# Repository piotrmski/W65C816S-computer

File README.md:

# W65C816S single-board computer

The following repository documents my novice attempt at designing a microprocessor single-board computer. I had fun putting this design together, however without any prior experience it's left with many flaws which should be addressed if anyone would want to implement it again.

It's a KiCad project, however a single-page PDF of the schematic and gerber files are included, so KiCad is not required to preview it.

### Specs

- W65C816S processor clocked at 10 MHz
- 504 KiB RAM
- 7.75 KiB ROM at half clock speed
- W65C22S peripheral device controller (VIA)
- Dual PS/2 input
- MicroSD input via SPI
- W65C22S's PA6, PA7, PB0-7, CB1, CB2 exposed as general purpose output, intended to drive a character display

### Address space

- 00000-0DFFF - 56 KiB of RAM intended for stack and direct page
- 0E000-0E0FF - I/O (4 least significant bits address VIA, bits 5-7 are unused)
- 0E100-0FFFF - 7.75 KiB of ROM
- 10000-7FFFF - 448 KiB of RAM

### What I think I did right

- It's simple.
- It's compact.
- It's fast.

### Quirks of the design

- In the PCB design many of the components are in DIP packages, my choice of DIP was motivated by the ability to prototype on breadboards.
- In the PCB design capacitors are relatively large to allow hand soldering; resistors are DIP because that's what I had on hand.
- 256 B of ROM (1/32) and 8 KiB of RAM (1/64) are wasted, however I consider it not a big deal.
- Not all SD cards support SPI interface.

### What I did wrong

- The ATF16V8Cs consume unreasonable amounts of energy, glue logic should have been designed with discrete logic gate components.
- Removing and replugging the entire ROM chip to flash it is too fiddly, a programming connector would make programming this device simpler.
- ROM is read only, however it would be simple enough to add a physical switch allowing the processor to write to ROM.

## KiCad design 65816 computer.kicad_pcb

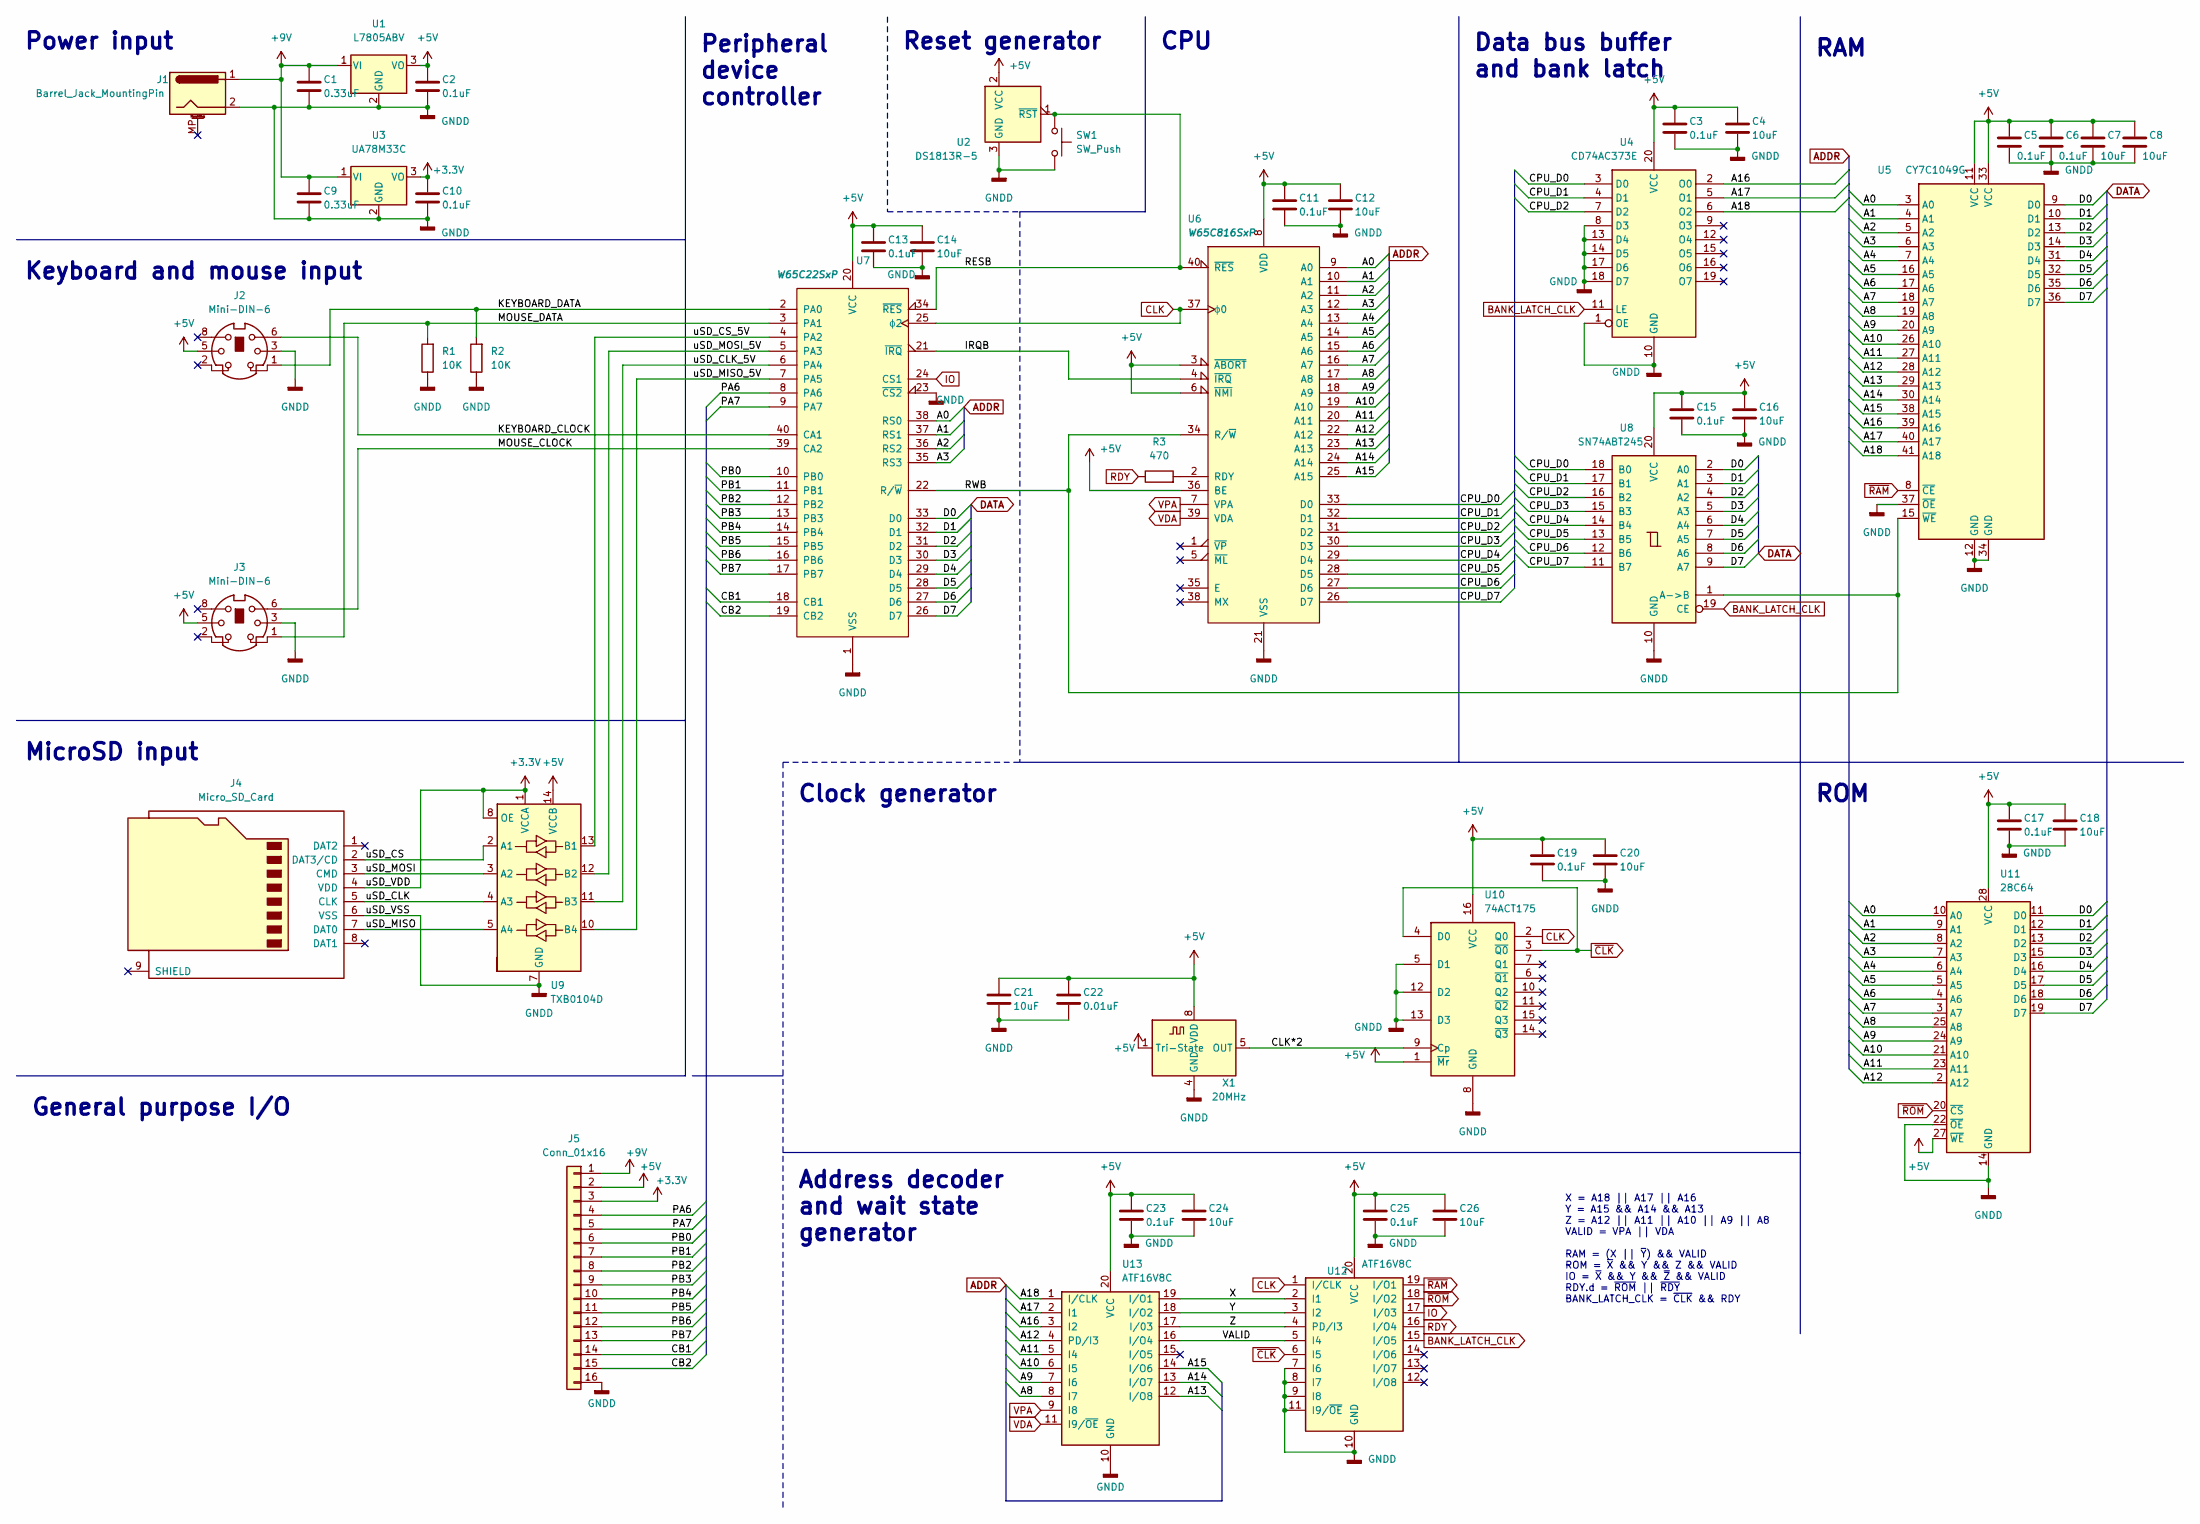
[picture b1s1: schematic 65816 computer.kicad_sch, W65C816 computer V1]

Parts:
C1, C9: 0.33uF; C_1206_3216Metric_Pad1.33x1.80mm_HandSolder
C2, C3, C5, C6, C10, C11, C13, C15, C17, C19, C23, C25: 0.1uF; C_1206_3216Metric_Pad1.33x1.80mm_HandSolder
C4, C7, C8, C12, C14, C16, C18, C20, C21, C24, C26: 10uF; C_1206_3216Metric_Pad1.33x1.80mm_HandSolder
C22: 0.01uF; C_1206_3216Metric_Pad1.33x1.80mm_HandSolder
J1: Barrel_Jack_MountingPin; BarrelJack_GCT_DCJ200-10-A_Horizontal
J2, J3: Mini-DIN-6; KMDGX6SBS
J4: Micro_SD_Card; microSD_HC_Wuerth_693072010801
J5: Conn_01x16; PinHeader_1x16_P2.54mm_Vertical
R1, R2: 10K; R_Axial_DIN0207_L6.3mm_D2.5mm_P7.62mm_Horizontal
R3: 470; R_Axial_DIN0207_L6.3mm_D2.5mm_P7.62mm_Horizontal
SW1: SW_Push; SW_PUSH_6mm
U1: L7805ABV; TO-220-3_Vertical
U2: DS1813R-5; SOT-23
U3: UA78M33C; TO-252-2
U4: CD74AC373E; DIP-20_W7.62mm_Socket_LongPads
U5: CY7C1049G; TSOP-II-44_10.16x18.41mm_P0.8mm
U6: W65C816SxP; DIP-40_W15.24mm_Socket_LongPads
U7: W65C22SxP; DIP-40_W15.24mm_Socket_LongPads
U8: SN74ABT245; DIP-20_W7.62mm_Socket_LongPads
U9: TXB0104D; SOIC-14_3.9x8.7mm_P1.27mm
U10: 74ACT175; DIP-16_W7.62mm_Socket_LongPads
U11: 28C64; DIP-28_W15.24mm_Socket_LongPads
U12, U13: ATF16V8C; DIP-20_W7.62mm_Socket_LongPads
X1: 20MHz; Oscillator_DIP-8

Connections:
+3V3: C10.1, J4.4 (VDD), J5.3, U3.3 (VO), U9.1 (VCCA), U9.8 (OE)
+5V: C2.1, C3.1, C4.1, C5.1, C6.1, C7.1, C8.1, C11.1, C12.1, C13.1, C14.1, C15.1, C16.1, C17.1, C18.1, C19.1, C20.1, C21.1, C22.1, C23.1, C24.1, C25.1, C26.1, J2.5, J3.5, J5.2, U1.3 (VO), U2.2 (VCC), U4.20 (VCC), U5.11 (VCC), U5.33 (VCC), U6.3 (~ABORT), U6.6 (~NMI), U6.8 (VDD), U6.36 (BE), U7.20 (VCC), U8.20 (VCC), U9.14 (VCCB), U10.1 (~Mr), U10.16 (VCC), U11.27 (~WE), U11.28 (VCC), U12.20 (VCC), U13.20 (VCC), X1.1 (Tri-State), X1.8 (VDD)
+9V: C1.1, C9.1, J1.1, J5.1, U1.1 (VI), U3.1 (VI)
/A0: U5.3 (A0), U6.9 (A0), U7.38 (RS0), U11.10 (A0)
/A1: U5.4 (A1), U6.10 (A1), U7.37 (RS1), U11.9 (A1)
/A2: U5.5 (A2), U6.11 (A2), U7.36 (RS2), U11.8 (A2)
/A3: U5.6 (A3), U6.12 (A3), U7.35 (RS3), U11.7 (A3)
/A4: U5.7 (A4), U6.13 (A4), U11.6 (A4)
/A5: U5.16 (A5), U6.14 (A5), U11.5 (A5)
/A6: U5.17 (A6), U6.15 (A6), U11.4 (A6)
/A7: U5.18 (A7), U6.16 (A7), U11.3 (A7)
/A8: U5.19 (A8), U6.17 (A8), U11.25 (A8), U13.8 (I7)
/A9: U5.20 (A9), U6.18 (A9), U11.24 (A9), U13.7 (I6)
/A10: U5.26 (A10), U6.19 (A10), U11.21 (A10), U13.6 (I5)
/A11: U5.27 (A11), U6.20 (A11), U11.23 (A11), U13.5 (I4)
/A12: U5.28 (A12), U6.22 (A12), U11.2 (A12), U13.4 (PD/I3)
/A13: U5.29 (A13), U6.23 (A13), U13.12 (I/O8)
/A14: U5.30 (A14), U6.24 (A14), U13.13 (I/O7)
/A15: U5.38 (A15), U6.25 (A15), U13.14 (I/O6)
/A16: U4.2 (O0), U5.39 (A16), U13.3 (I2)
/A17: U4.5 (O1), U5.40 (A17), U13.2 (I1)
/A18: U4.6 (O2), U5.41 (A18), U13.1 (I/CLK)
/CB1: J5.14, U7.18 (CB1)
/CB2: J5.15, U7.19 (CB2)
/CLK*2: U10.9 (Cp), X1.5 (OUT)
/CPU_D0: U4.3 (D0), U6.33 (D0), U8.18 (B0)
/CPU_D1: U4.4 (D1), U6.32 (D1), U8.17 (B1)
/CPU_D2: U4.7 (D2), U6.31 (D2), U8.16 (B2)
/CPU_D3: U6.30 (D3), U8.15 (B3)
/CPU_D4: U6.29 (D4), U8.14 (B4)
/CPU_D5: U6.28 (D5), U8.13 (B5)
/CPU_D6: U6.27 (D6), U8.12 (B6)
/CPU_D7: U6.26 (D7), U8.11 (B7)
/D0: U5.9 (D0), U7.33 (D0), U8.2 (A0), U11.11 (D0)
/D1: U5.10 (D1), U7.32 (D1), U8.3 (A1), U11.12 (D1)
/D2: U5.13 (D2), U7.31 (D2), U8.4 (A2), U11.13 (D2)
/D3: U5.14 (D3), U7.30 (D3), U8.5 (A3), U11.15 (D3)
/D4: U5.31 (D4), U7.29 (D4), U8.6 (A4), U11.16 (D4)
/D5: U5.32 (D5), U7.28 (D5), U8.7 (A5), U11.17 (D5)
/D6: U5.35 (D6), U7.27 (D6), U8.8 (A6), U11.18 (D6)
/D7: U5.36 (D7), U7.26 (D7), U8.9 (A7), U11.19 (D7)
/IRQB: U6.4 (~IRQ), U7.21 (~IRQ)
/KEYBOARD_CLOCK: J2.6, U7.40 (CA1)
/KEYBOARD_DATA: J2.1, R2.2, U7.2 (PA0)
/MOUSE_CLOCK: J3.6, U7.39 (CA2)
/MOUSE_DATA: J3.1, R1.2, U7.3 (PA1)
/PA6: J5.4, U7.8 (PA6)
/PA7: J5.5, U7.9 (PA7)
/PB0: J5.6, U7.10 (PB0)
/PB1: J5.7, U7.11 (PB1)
/PB2: J5.8, U7.12 (PB2)
/PB3: J5.9, U7.13 (PB3)
/PB4: J5.10, U7.14 (PB4)
/PB5: J5.11, U7.15 (PB5)
/PB6: J5.12, U7.16 (PB6)
/PB7: J5.13, U7.17 (PB7)
/RESB: SW1.1, U2.1 (~RST), U6.40 (~RES), U7.34 (~RES)
/RWB: U5.15 (~WE), U6.34 (R/~W), U7.22 (R/~W), U8.1 (A->B)
/VALID: U12.5 (I4), U13.16 (I/O4)
/X: U12.2 (I1), U13.19 (I/O1)
/Y: U12.3 (I2), U13.18 (I/O2)
/Z: U12.4 (PD/I3), U13.17 (I/03)
/uSD_CLK: J4.5 (CLK), U9.4 (A3)
/uSD_CLK_5V: U7.6 (PA4), U9.11 (B3)
/uSD_CS: J4.2 (DAT3/CD), U9.2 (A1)
/uSD_CS_5V: U7.4 (PA2), U9.13 (B1)
/uSD_MISO: J4.7 (DAT0), U9.5 (A4)
/uSD_MISO_5V: U7.7 (PA5), U9.10 (B4)
/uSD_MOSI: J4.3 (CMD), U9.3 (A2)
/uSD_MOSI_5V: U7.5 (PA3), U9.12 (B2)
BANK_LATCH_CLK: U4.11 (LE), U8.19 (CE), U12.15 (I/O5)
CLK: U6.37 (ϕ0), U7.25 (ϕ2), U10.2 (Q0), U12.1 (I/CLK)
IO: U7.24 (CS1), U12.17 (I/03)
unnamed: R3.2, U6.2 (RDY)
RDY: R3.1, U12.16 (I/O4)
VDA: U6.39 (VDA), U13.11 (I9/~OE)
VPA: U6.7 (VPA), U13.9 (I8)
~CLK: U10.3 (~Q0), U10.4 (D0), U12.6 (I5)
~RAM: U5.8 (~CE), U12.19 (I/O1)
~ROM: U11.20 (~CS), U12.18 (I/O2)

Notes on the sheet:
ROM
Reset generator
Clock generator
Address decoder and wait state generator
Data bus buffer and bank latch
Power input
General purpose I/O
Keyboard and mouse input
RAM
MicroSD input
CPU
Peripheral device controller
X = A18 || A17 || A16 Y = A15 && A14 && A13 Z = A12 || A11 || A10 || A9 || A8 VALID = VPA || VDA RAM = (X || ~{Y}) && VALID ROM = ~{X} && Y && Z && VALID IO = ~{X} && Y && ~{Z} && VALID RDY.d = ~{ROM} || ~{RDY} BANK_LATCH_CLK = ~{CLK} && RDY

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
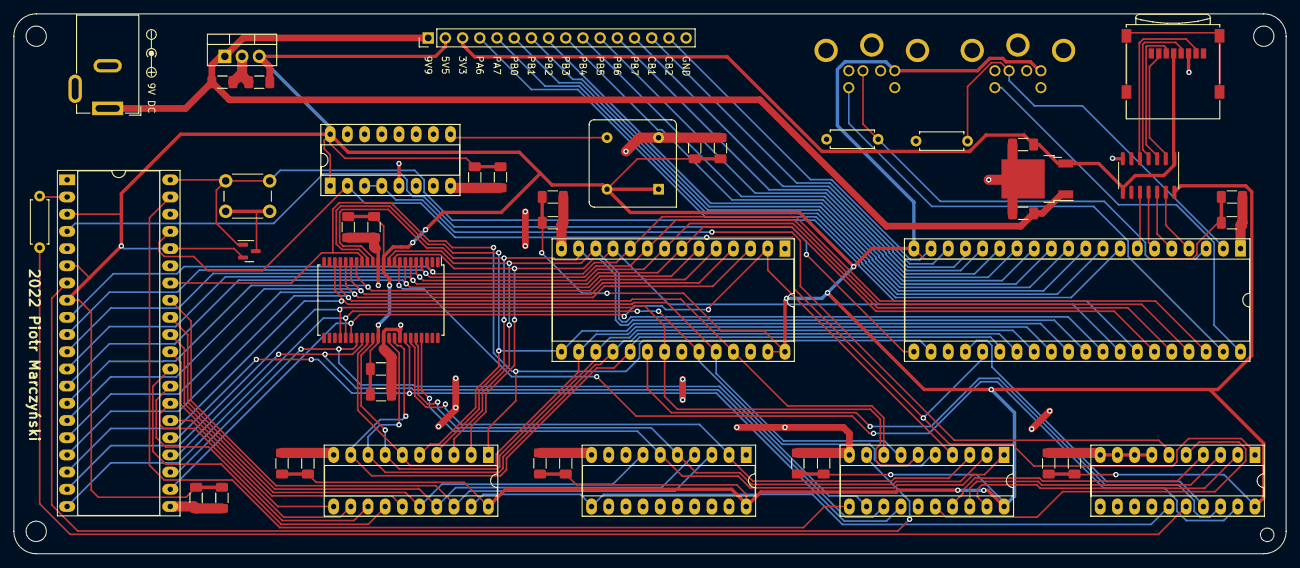
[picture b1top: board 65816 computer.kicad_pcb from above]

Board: 2 copper layers, 188.0 x 79.8 mm, 49 parts (0 on the bottom side), 81 nets.

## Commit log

2023-03-29 Init
2023-04-03 Added photo
